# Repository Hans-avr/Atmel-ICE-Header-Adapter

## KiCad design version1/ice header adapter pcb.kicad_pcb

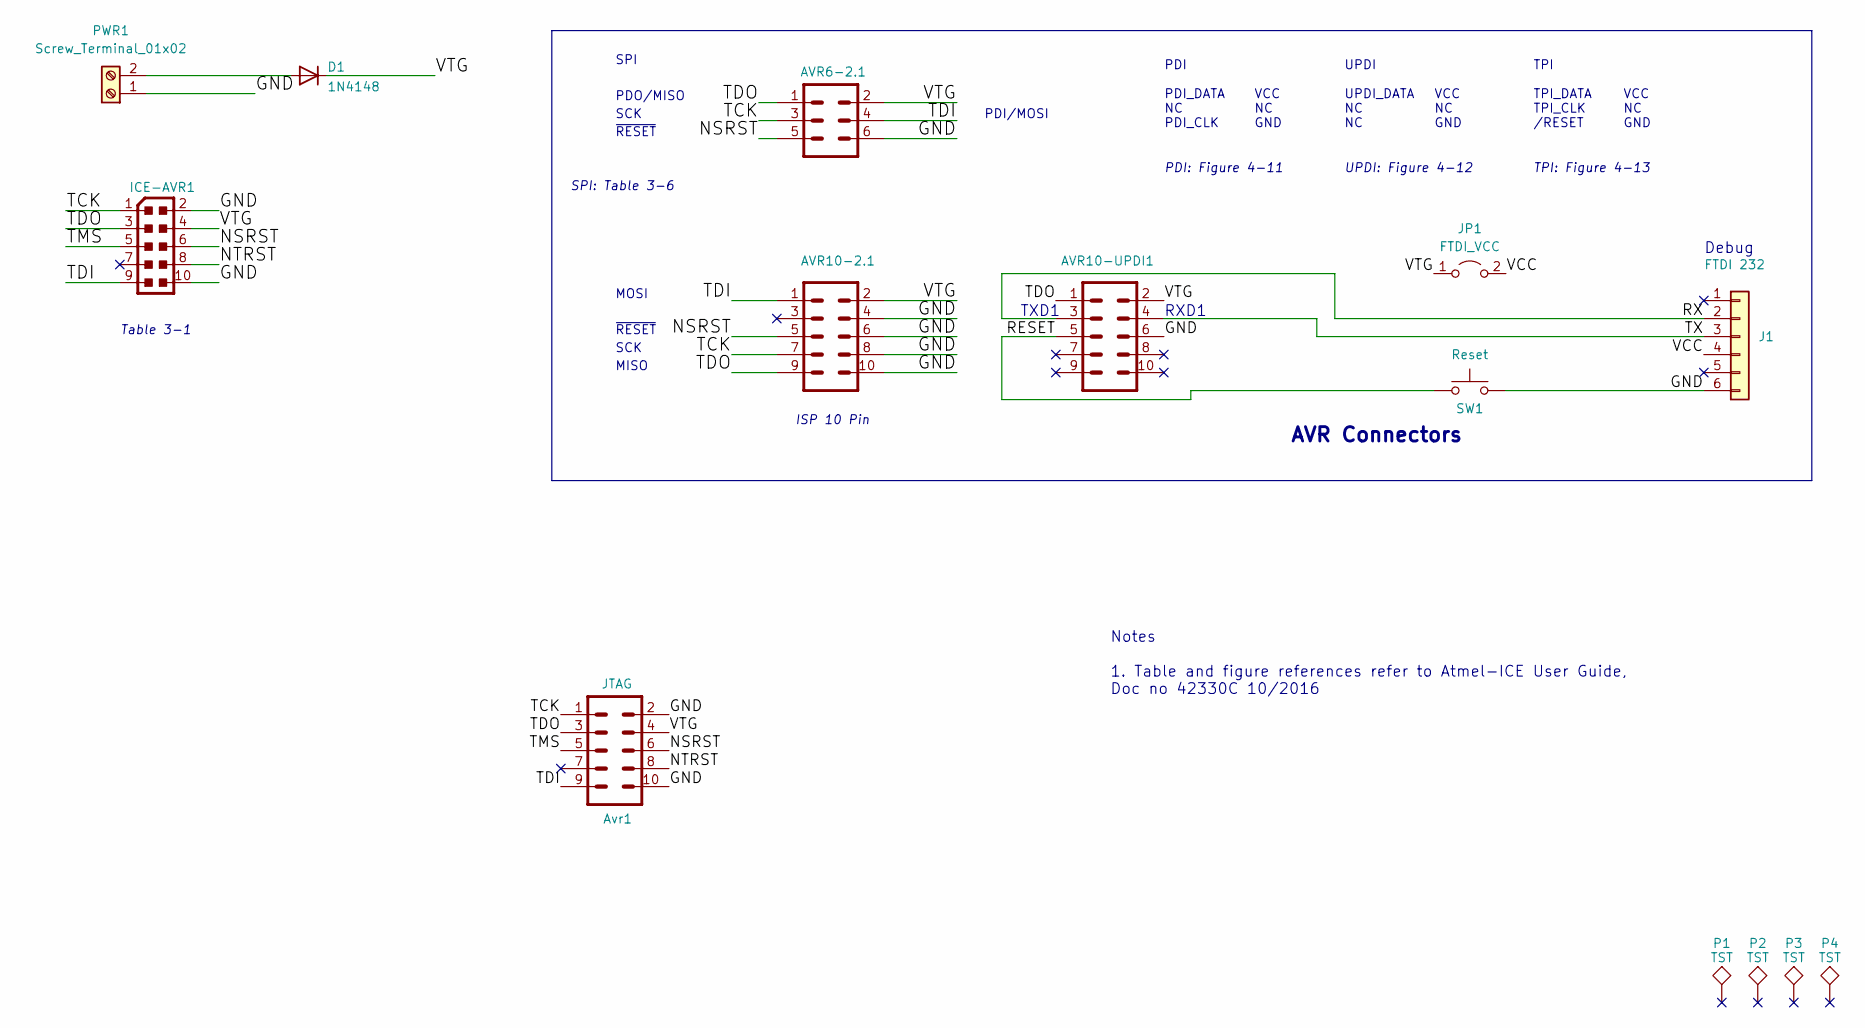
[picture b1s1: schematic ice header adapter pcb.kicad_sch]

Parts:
AVR6-2.1: ML6
AVR10-2.1, AVR10-UPDI1: ML10
Avr1: JTAG; ML10
D1: 1N4148; DO35-7
ICE-AVR1: PINHEAD_PINHD-2X5; PINHEAD_2X05_127
J1: FTDI 232; PinSocket_1x06_P2.54mm_Vertical
JP1: FTDI_VCC; PinSocket_1x02_P2.54mm_Vertical
P1, P2, P3, P4: TST; MountingHole_2.7mm_M2.5
PWR1: Screw_Terminal_01x02; PhoenixContact_MSTBA_2,5_2-G-5,08_1x02_P5.08mm_Horizontal
SW1: Reset; SW_PUSH_6mm_H5mm

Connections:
/GND: AVR6-2.1.6, AVR10-2.1.4, AVR10-2.1.6, AVR10-2.1.8, AVR10-2.1.10, AVR10-UPDI1.6, Avr1.2, Avr1.10, ICE-AVR1.2, ICE-AVR1.10, J1.6, PWR1.1, SW1.2; also elsewhere on the board
/NSRST: AVR6-2.1.5, AVR10-2.1.5, Avr1.6, ICE-AVR1.6
/NTRST: Avr1.8, ICE-AVR1.8
/RESET: AVR10-UPDI1.5, SW1.1; also elsewhere on the board
/RX: AVR10-UPDI1.3, J1.2; also elsewhere on the board
/TCK: AVR6-2.1.3, AVR10-2.1.7, Avr1.1, ICE-AVR1.1
/TDI: AVR6-2.1.4, AVR10-2.1.1, Avr1.9, ICE-AVR1.9
/TDO: AVR6-2.1.1, AVR10-2.1.9, AVR10-UPDI1.1, Avr1.3, ICE-AVR1.3; also elsewhere on the board
/TMS: Avr1.5, ICE-AVR1.5
/TX: AVR10-UPDI1.4, J1.3; also elsewhere on the board
/VCC: J1.4, JP1.2 (B)
/VTG: AVR6-2.1.2, AVR10-2.1.2, AVR10-UPDI1.2, Avr1.4, D1.C, ICE-AVR1.4, JP1.1 (A); also elsewhere on the board
unnamed: D1.A, PWR1.2

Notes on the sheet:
~{RESET}
SPI: Table 3-6
VCC NC GND
SPI
PDI PDI_DATA NC PDI_CLK
VCC NC GND
SCK
UPDI UPDI_DATA NC NC
MOSI
Debug
TPI TPI_DATA TPI_CLK /RESET
UPDI: Figure 4-12
AVR Connectors
TXD1
PDO/MISO
MISO
Notes 1. Table and figure references refer to Atmel-ICE User Guide, Doc no 42330C 10/2016
PDI: Figure 4-11
ISP 10 Pin
Table 3-1
PDI/MOSI
RXD1
TPI: Figure 4-13

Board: 2 copper layers, 14 parts (0 on the bottom side), 13 nets, no tracks yet.

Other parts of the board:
UPDI: ML10

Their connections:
/GND: UPDI.6; also elsewhere on the board
/RESET: UPDI.5; also elsewhere on the board
/RX: UPDI.3; also elsewhere on the board
/TDO: UPDI.1; also elsewhere on the board
/TX: UPDI.4; also elsewhere on the board
/VTG: UPDI.2; also elsewhere on the board

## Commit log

2022-02-10 UPDI -ISP
    SAM delete
    UPDI 10p. added
2022-02-12 weiter am pc
